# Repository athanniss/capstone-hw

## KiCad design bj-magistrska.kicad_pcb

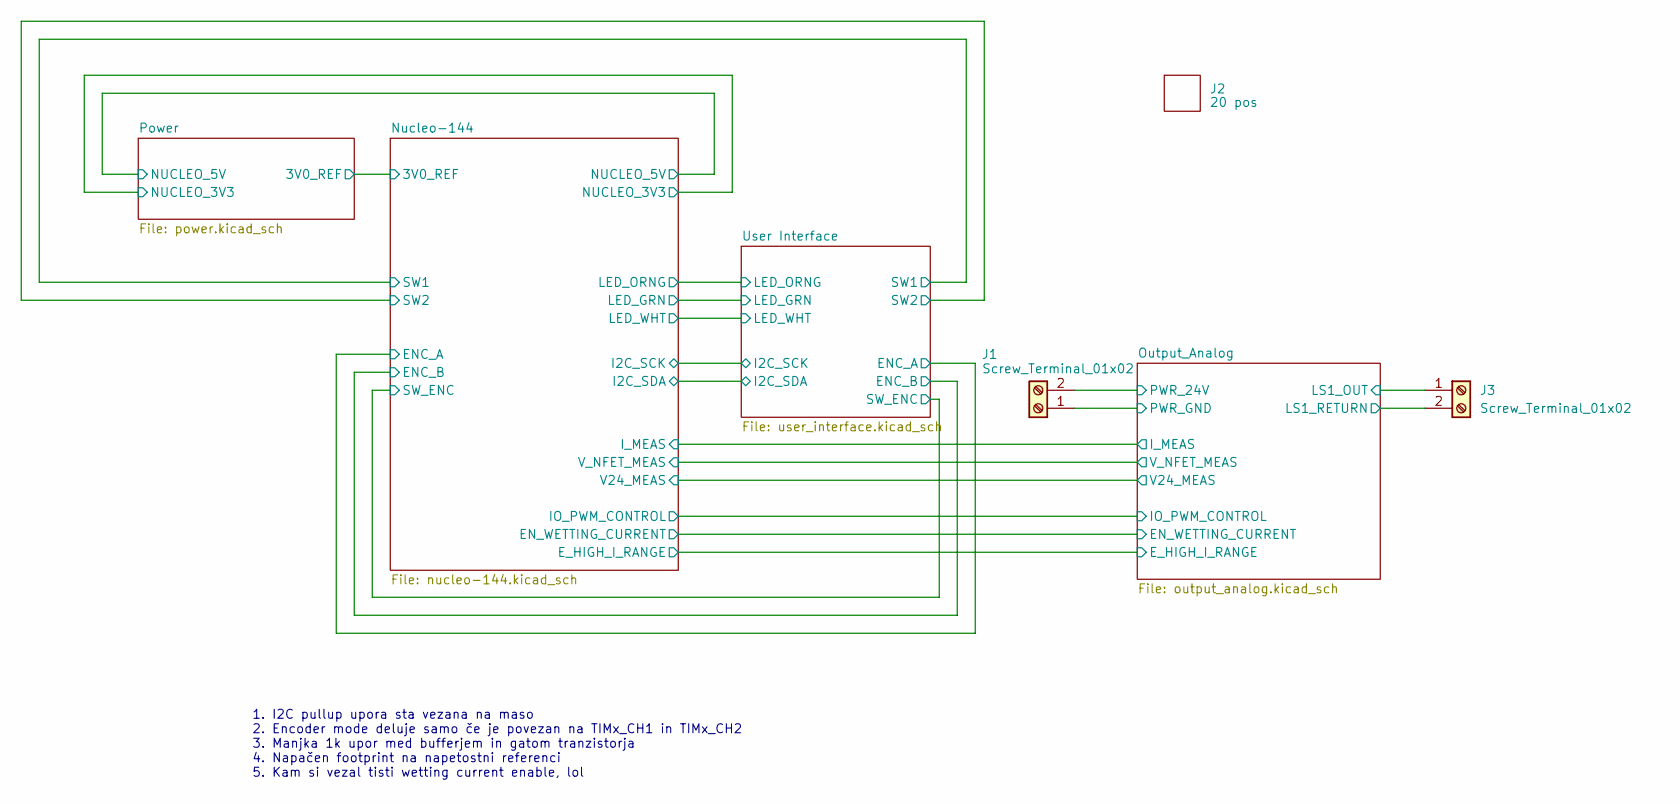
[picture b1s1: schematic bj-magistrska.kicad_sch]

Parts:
J1, J3: Screw_Terminal_01x02; TerminalBlock_Phoenix_MKDS-1,5-2-5.08_1x02_P5.08mm_Horizont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; Mfg. Part Number 1985904
J2: 20 pos; Mfg. Part Number PRPC020SACN-RC; Digikey no. S1131EC-20-ND

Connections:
/Output_Analog/LS1_OUT: J1.2, J3.1; also elsewhere on the board
/Output_Analog/LS1_RETURN: J3.2; also elsewhere on the board
/Output_Analog/PWR_GND: J1.1; also elsewhere on the board

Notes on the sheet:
1. I2C pullup upora sta vezana na maso 2. Encoder mode deluje samo če je povezan na TIMx_CH1 in TIMx_CH2 3. Manjka 1k upor med bufferjem in gatom tranzistorja 4. Napačen footprint na napetostni referenci 5. Kam si vezal tisti wetting current enable, lol

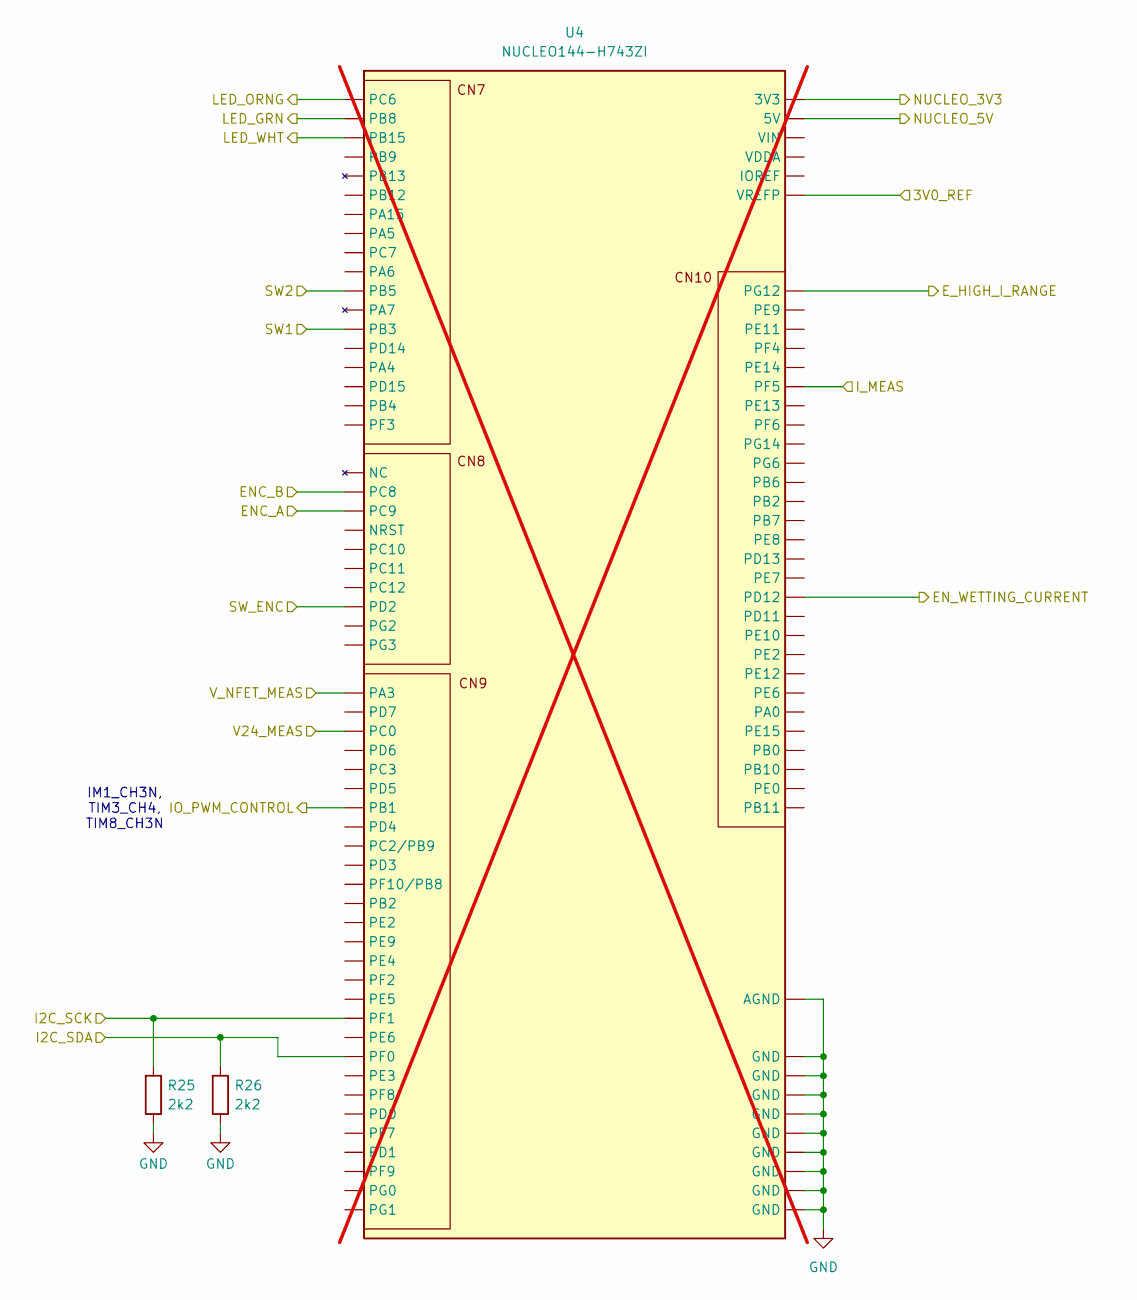
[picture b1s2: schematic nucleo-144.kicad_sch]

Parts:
R25, R26: 2k2; R_0603_1608Metric
U4: NUCLEO144-H743ZI; ST_Zio_Only_Connectors_144_STLink; not fitted

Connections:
+3V3: U4.CN8_7 (3V3); also elsewhere on the board
+5VD: U4.CN8_9 (5V); also elsewhere on the board
/Nucleo-144/3V0_REF: U4.CN7_6 (VREFP); also elsewhere on the board
/Nucleo-144/ENC_A: U4.CN8_4 (PC9); also elsewhere on the board
/Nucleo-144/ENC_B: U4.CN8_2 (PC8); also elsewhere on the board
/Nucleo-144/EN_WETTING_CURRENT: U4.CN10_21 (PD12); also elsewhere on the board
/Nucleo-144/E_HIGH_I_RANGE: U4.CN10_2 (PG12); also elsewhere on the board
/Nucleo-144/I2C_SCK: R25.1, U4.CN9_19 (PF1); also elsewhere on the board
/Nucleo-144/I2C_SDA: R26.1, U4.CN9_21 (PF0); also elsewhere on the board
/Nucleo-144/IO_PWM_CONTROL: U4.CN9_7 (РВ1); also elsewhere on the board
/Nucleo-144/I_MEAS: U4.CN10_9 (PF5); also elsewhere on the board
/Nucleo-144/LED_GRN: U4.CN7_2 (PB8); also elsewhere on the board
/Nucleo-144/LED_ORNG: U4.CN7_1 (PC6); also elsewhere on the board
/Nucleo-144/LED_WHT: U4.CN7_3 (PB15); also elsewhere on the board
/Nucleo-144/SW1: U4.CN7_15 (PB3); also elsewhere on the board
/Nucleo-144/SW2: U4.CN7_13 (PB5); also elsewhere on the board
/Nucleo-144/SW_ENC: U4.CN8_12 (PD2); also elsewhere on the board
/Nucleo-144/V24_MEAS: U4.CN9_3 (PC0); also elsewhere on the board
/Nucleo-144/V_NFET_MEAS: U4.CN9_1 (РАЗ); also elsewhere on the board
GND: R25.2, R26.2, U4.CN7_8 (GND), U4.CN8_11 (GND), U4.CN8_13 (GND), U4.CN9_12 (GND), U4.CN9_23 (GND), U4.CN10_3 (AGND), U4.CN10_5 (GND), U4.CN10_17 (GND), U4.CN10_22 (GND), U4.CN10_27 (GND); also elsewhere on the board

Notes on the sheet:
IM1_CH3N, TIM3_CH4, TIM8_CH3N

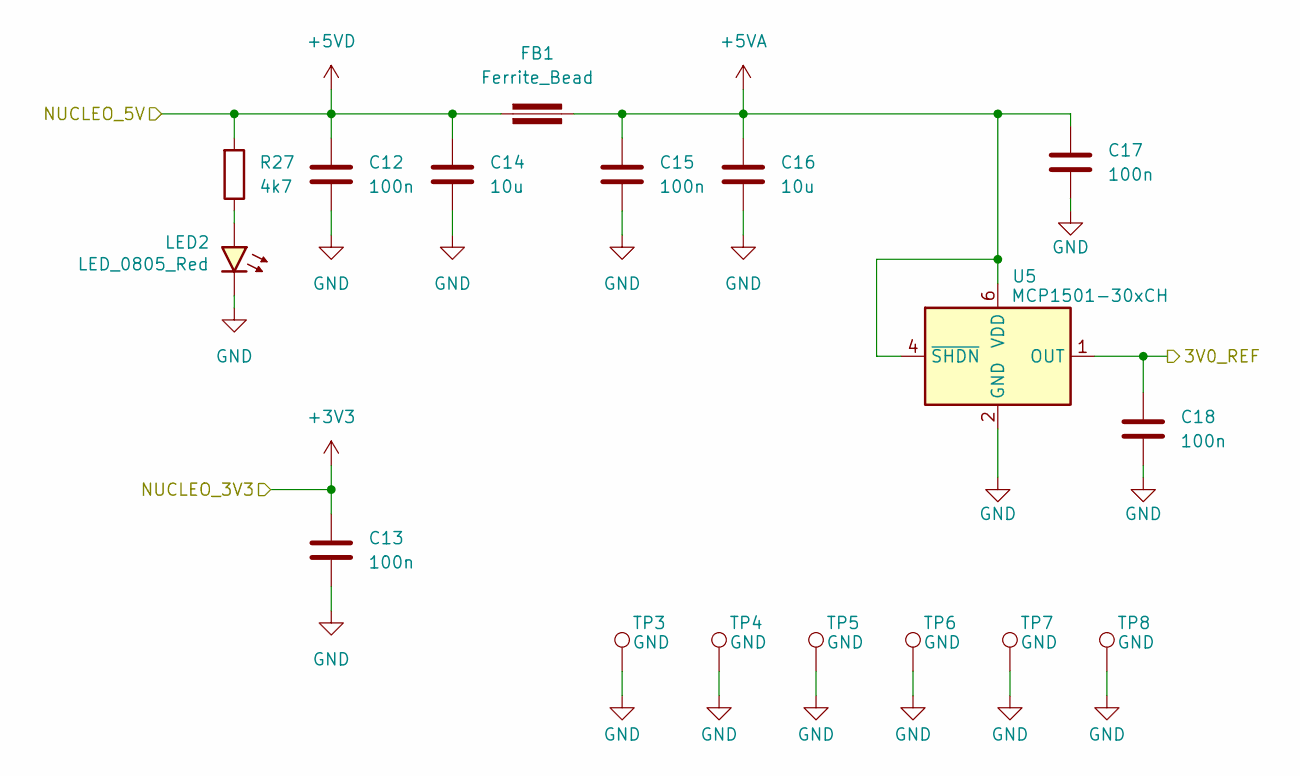
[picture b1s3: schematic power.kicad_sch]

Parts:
C12, C13, C15, C17, C18: 100n; C_0603_1608Metric
C14, C16: 10u; C_0805_2012Metric
FB1: Ferrite_Bead; Ferrite_0603_1608Metric
LED2: LED_0805_Red; LED_0805_2012Metric
R27: 4k7; R_0603_1608Metric
TP3, TP4, TP5, TP6, TP7, TP8: GND; TestPoint_THTPad_D1.0mm_Drill0.5mm
U5: MCP1501-30xCH; SOT-23-6; Mfg. Part Number MCP1501-30E/SN

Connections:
+3V3: C13.1; also elsewhere on the board
+5VA: C15.1, C16.1, C17.1, FB1.2, U5.4 (~SHDN), U5.6 (VDD); also elsewhere on the board
+5VD: C12.1, C14.1, FB1.1, R27.1; also elsewhere on the board
/Nucleo-144/3V0_REF: C18.1, U5.1 (OUT); also elsewhere on the board
GND: C12.2, C13.2, C14.2, C15.2, C16.2, C17.2, C18.2, LED2.1 (K), TP3.1, TP4.1, TP5.1, TP6.1, TP7.1, TP8.1, U5.2 (GND), U5.3 (GND), U5.5 (GND); also elsewhere on the board
unnamed: LED2.2 (A), R27.2

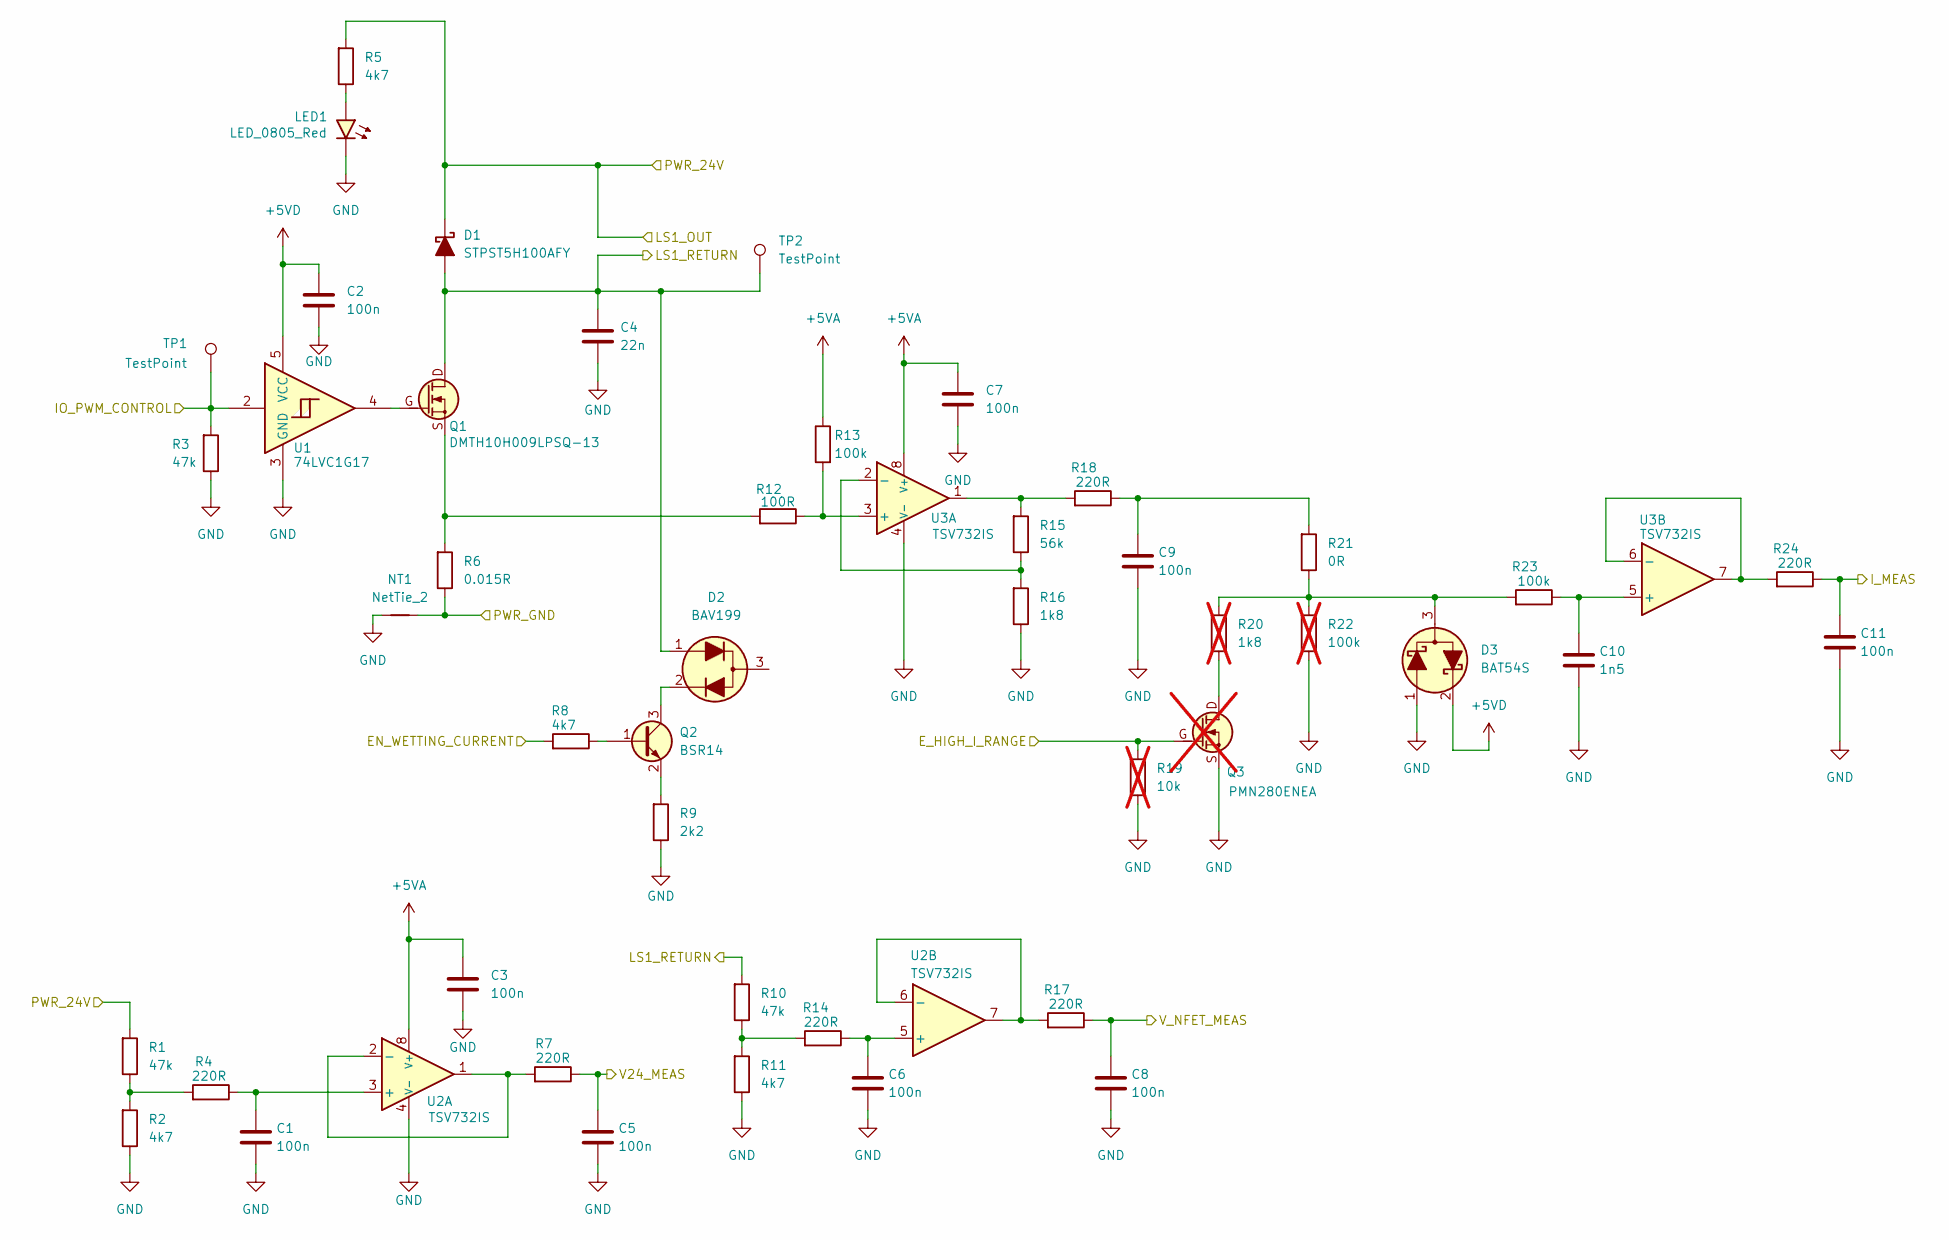
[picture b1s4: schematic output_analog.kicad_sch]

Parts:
C1, C2, C3, C5, C6, C7, C8, C9, C11: 100n; C_0603_1608Metric
C4: 22n; C_0603_1608Metric
C10: 1n5; C_0603_1608Metric
D1: STPST5H100AFY; D_SOD-128; Mfg. Part Number STPST5H100AFY
D2: BAV199; SOT-23; Mfg. Part Number BAV199
D3: BAT54S; SOT-23; Mfg. Part Number BAT54SHYT116
LED1: LED_0805_Red; LED_0805_2012Metric
NT1: NetTie_2; NetTie-2_THT_Pad0.3mm
Q1: DMTH10H009LPSQ-13; Diodes_PowerDI5060-8_ThermalVias; Mfg. Part Number DMTH10H009LPSQ-13
Q2: BSR14; SOT-23; Mfg. Part Number BSR14
Q3: PMN280ENEA; SC-74-6_1.5x2.9mm_P0.95mm; Mfg. Part Number PMN280ENEAX; not fitted
R1, R3, R10: 47k; R_0603_1608Metric
R2, R5, R8, R11: 4k7; R_0603_1608Metric
R4, R7, R14, R17, R18, R24: 220R; R_0603_1608Metric
R6: 0.015R; R_1206_3216Metric; Mfg. Part Number MFSA1206R0150FCM
R9: 2k2; R_0603_1608Metric
R12: 100R; R_0603_1608Metric
R13, R23: 100k; R_0603_1608Metric
R15: 56k; R_0603_1608Metric
R16: 1k8; R_0603_1608Metric
R19: 10k; R_0603_1608Metric; not fitted
R20: 1k8; R_0603_1608Metric; not fitted
R21: 0R; R_0603_1608Metric
R22: 100k; R_0603_1608Metric; not fitted
TP1, TP2: TestPoint; TestPoint_THTPad_D1.0mm_Drill0.5mm
U1: 74LVC1G17; SOT-23-5; Mfg. Part Number SN74LVC1G17DBVR
U2, U3: TSV732IS; MSOP-8_3x3mm_P0.65mm; Mfg. Part Number TSV732IST

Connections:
+5VA: C3.1, C7.1, R13.2, U2.8 (V+), U3.8 (V+); also elsewhere on the board
+5VD: C2.1, D3.2 (K), U1.5 (VCC); also elsewhere on the board
/Nucleo-144/EN_WETTING_CURRENT: R8.1; also elsewhere on the board
/Nucleo-144/E_HIGH_I_RANGE: Q3.G, R19.1; also elsewhere on the board
/Nucleo-144/IO_PWM_CONTROL: R3.1, TP1.1, U1.2; also elsewhere on the board
/Nucleo-144/I_MEAS: C11.1, R24.2; also elsewhere on the board
/Nucleo-144/V24_MEAS: C5.1, R7.2; also elsewhere on the board
/Nucleo-144/V_NFET_MEAS: C8.1, R17.2; also elsewhere on the board
/Output_Analog/LS1_OUT: D1.1 (K), R1.1, R5.1; also elsewhere on the board
/Output_Analog/LS1_RETURN: C4.1, D1.2 (A), D2.1 (A), Q1.D, R10.1, TP2.1; also elsewhere on the board
/Output_Analog/PWR_GND: NT1.2, R6.2; also elsewhere on the board
GND: C1.2, C2.2, C3.2, C4.2, C5.2, C6.2, C7.2, C8.2, C9.2, C10.2, C11.2, D3.1 (A), LED1.1 (K), NT1.1, Q3.S, R2.2, R3.2, R9.2, R11.2, R16.2, R19.2, R22.2, U1.3 (GND), U2.4 (V-), U3.4 (V-); also elsewhere on the board
unnamed: C9.1, R18.2, R21.1
unnamed: D2.2 (K), Q2.3 (C)
unnamed: D3.3 (C), R20.1, R21.2, R22.1, R23.1
unnamed: LED1.2 (A), R5.2
unnamed: Q1.G, U1.4
unnamed: Q1.S, R6.1, R12.1
unnamed: Q2.1 (B), R8.2
unnamed: Q2.2 (E), R9.1
unnamed: Q3.D, R20.2
unnamed: R1.2, R2.1, R4.1
unnamed: R10.2, R11.1, R14.1
unnamed: R15.1, R18.1, U3.1
unnamed: C1.1, R4.2, U2.3 (+)
unnamed: R7.1, U2.1, U2.2 (-)
unnamed: C6.1, R14.2, U2.5 (+)
unnamed: R17.1, U2.6 (-), U2.7
unnamed: R12.2, R13.1, U3.3 (+)
unnamed: R15.2, R16.1, U3.2 (-)
unnamed: C10.1, R23.2, U3.5 (+)
unnamed: R24.1, U3.6 (-), U3.7

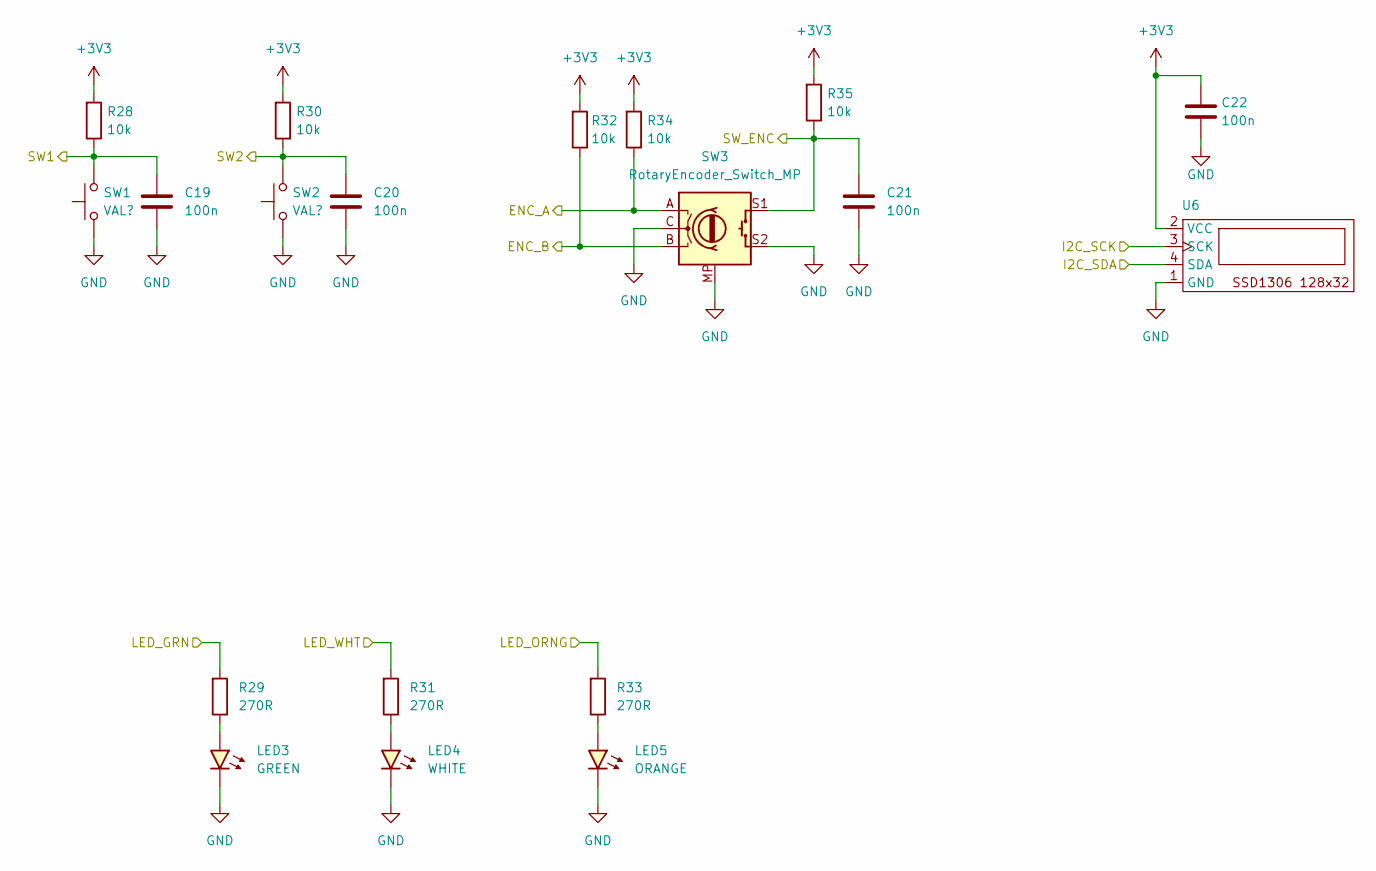
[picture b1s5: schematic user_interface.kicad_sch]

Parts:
C19, C20, C21, C22: 100n; C_0603_1608Metric
LED3: GREEN; LED_0805_2012Metric
LED4: WHITE; LED_0805_2012Metric
LED5: ORANGE; LED_0805_2012Metric
R28, R30, R32, R34, R35: 10k; R_0603_1608Metric
R29, R31, R33: 270R; R_0603_1608Metric
SW1, SW2: VAL?; SW_SPST_PTS647_Sx70; Mfg. Part Number PTS647SK70SMTR2LFS
SW3: RotaryEncoder_Switch_MP; RotaryEncoder_Alps_EC11E18244A5; Mfg. Part Number EC11E18244A5
U6: SSD1306-0.91-OLED-4pin-128x32_no-header-offset

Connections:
+3V3: C22.1, R28.1, R30.1, R32.1, R34.1, R35.1, U6.2 (VCC); also elsewhere on the board
/Nucleo-144/ENC_A: R34.2, SW3.A; also elsewhere on the board
/Nucleo-144/ENC_B: R32.2, SW3.B; also elsewhere on the board
/Nucleo-144/I2C_SCK: U6.3 (SCK); also elsewhere on the board
/Nucleo-144/I2C_SDA: U6.4 (SDA); also elsewhere on the board
/Nucleo-144/LED_GRN: R29.1; also elsewhere on the board
/Nucleo-144/LED_ORNG: R33.1; also elsewhere on the board
/Nucleo-144/LED_WHT: R31.1; also elsewhere on the board
/Nucleo-144/SW1: C19.1, R28.2, SW1.2; also elsewhere on the board
/Nucleo-144/SW2: C20.1, R30.2, SW2.2; also elsewhere on the board
/Nucleo-144/SW_ENC: C21.1, R35.2, SW3.S1; also elsewhere on the board
GND: C19.2, C20.2, C21.2, C22.2, LED3.1 (K), LED4.1 (K), LED5.1 (K), SW1.1, SW2.1, SW3.C, SW3.MP, SW3.S2, U6.1 (GND); also elsewhere on the board
unnamed: LED3.2 (A), R29.2
unnamed: LED4.2 (A), R31.2
unnamed: LED5.2 (A), R33.2

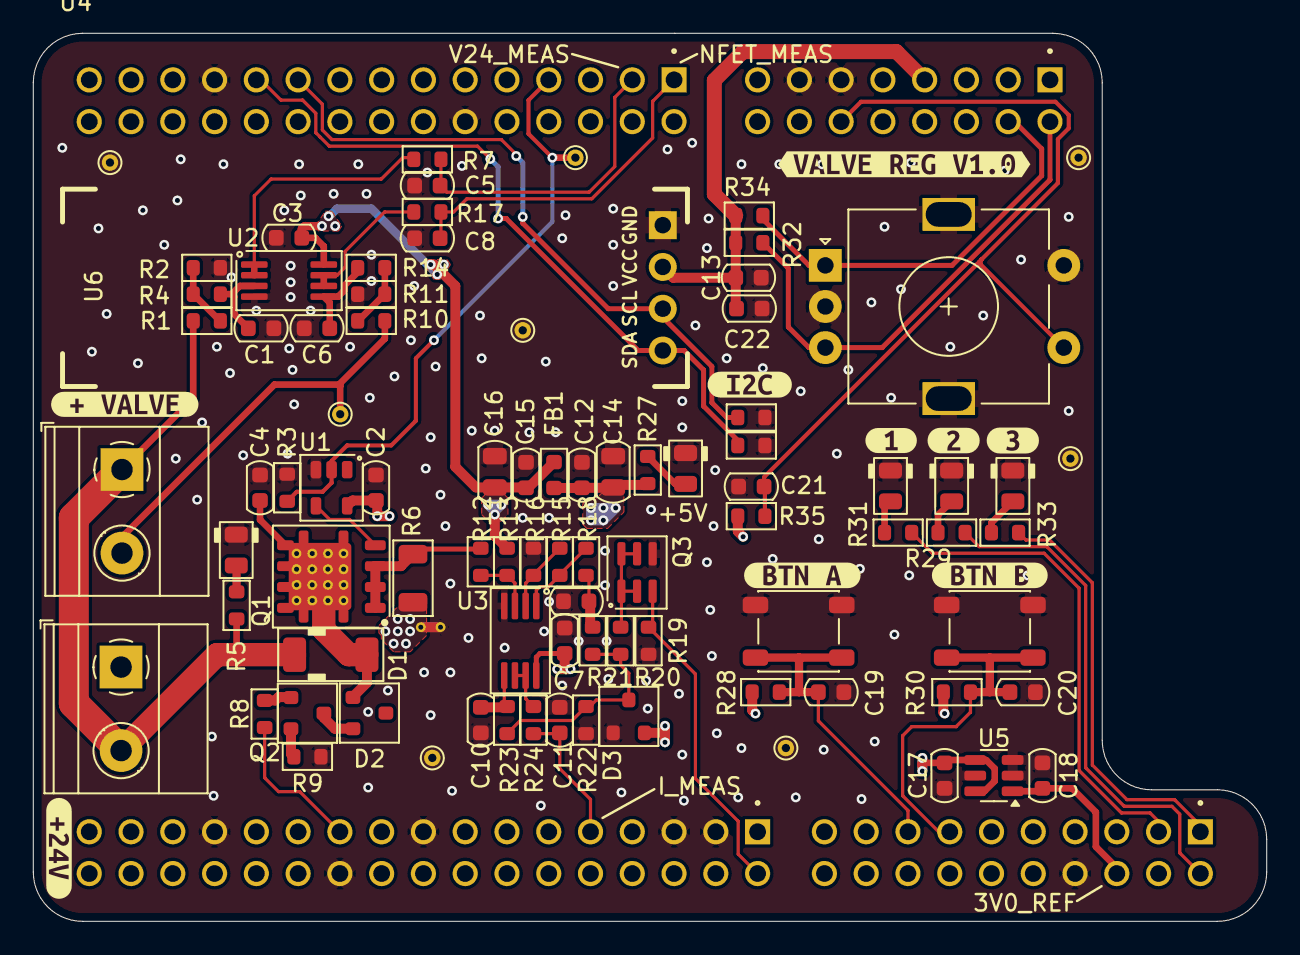
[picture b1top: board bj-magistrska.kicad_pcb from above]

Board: 4 copper layers, 75.0 x 54.0 mm, 98 parts (0 on the bottom side), 48 nets.

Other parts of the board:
kibuzzard-66E6F4AB: G***; kibuzzard-66E6F4AB
kibuzzard-66E6F4D2: G***; kibuzzard-66E6F4D2
kibuzzard-66E6F4F3: G***; kibuzzard-66E6F4F3
kibuzzard-66E6F41C: G***; kibuzzard-66E6F41C
kibuzzard-66E6F48A: G***; kibuzzard-66E6F48A
kibuzzard-66E6F432: G***; kibuzzard-66E6F432
kibuzzard-66E6F459: G***; kibuzzard-66E6F459
kibuzzard-66E6F464: G***; kibuzzard-66E6F464
kibuzzard-66E6F497: G***; kibuzzard-66E6F497

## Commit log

2025-02-03 Removed software from hardware repository. Now in separate repo.
